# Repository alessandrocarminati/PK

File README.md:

# Password keeper 
The password keeper is a toy device for storing the personal password, and type them quickly.
The device can store up to 8 different passwords, no more than 16 chars each with 8 tags no more than 8 chars each.
One of the two buttons on the device allows the user to select the intended password and while the other allows to type it.
One two lines Hitachi HD44780 compatible display allows the user to see the tag associated with the password before typing it.
Relevant features of this project are as follows:
* The main MCU is an AVR ATTINY 85 @16MHz
* Just one MCU GPIO is used to drive the display
* The device presents itself as a keyboard, and it allows using just the USB keyboard interface to update the password DB

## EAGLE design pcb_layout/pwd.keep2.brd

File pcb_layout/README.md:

#Password keeper PCB
The current repository implements the following schema

Because it is printed by hand, an effort is made to keep it single face.

Here the routed PCB

# BOM
| ID | Name     | Package      | Qty | Designation
|----|----------|--------------|-----|-------------
|  1 | IC1      | DIL16        |   1 | 74HC595N
|  2 | IC2      | DIL08        |   1 | ATtiny85-20PU
|  3 | IC3      | DIL14        |   1 | CD40106BCN
|  4 | R1, R2   | 0207/10      |   2 | 68 $\Omega$
|  5 | R3       | 0207/10      |   1 | 33k $\Omega$
|  6 | R4       | 0207/10      |   1 | 220k $\Omega$
|  7 | R5       | 0207/10      |   1 | 560 $\Omega$ 
|  8 | R6, R7   | 0207/10      |   2 | 10k $\Omega$
|  9 | R10      | 0207/10      |   1 | 1.5k $\Omega$ 
| 10 | R11      | 0207/10      |   1 | 470 $\Omega$ 
| 11 | D1       | DO35         |   1 | 1N581
| 12 | D2, D3   | DO35         |   2 | 1N5227B-TR
| 13 | LED1     | LED5MM       |   1 | Power
| 14 | LED2     | LED5MM       |   1 | ACT
| 15 | C1       | E2-5         |   1 | 10$\mu$F
| 16 | C2, C3   | C050-024X044 |   2 | 2.2nF
| 17 | J1       | 2X07_LOCK    |   1 | Display Connector
| 18 | JP3      | USB-B-PTH    |   1 | USB-B
| 19 | JP2      | 1X02_LOCK    |   1 | Reset
| 20 | JP4      | 1X02_LOCK    |   1 | Button1
| 21 | JP5      | 1X02_LOCK    |   1 | Button2
| 22 | DISPLAY  | NA           |   1 | LM16211

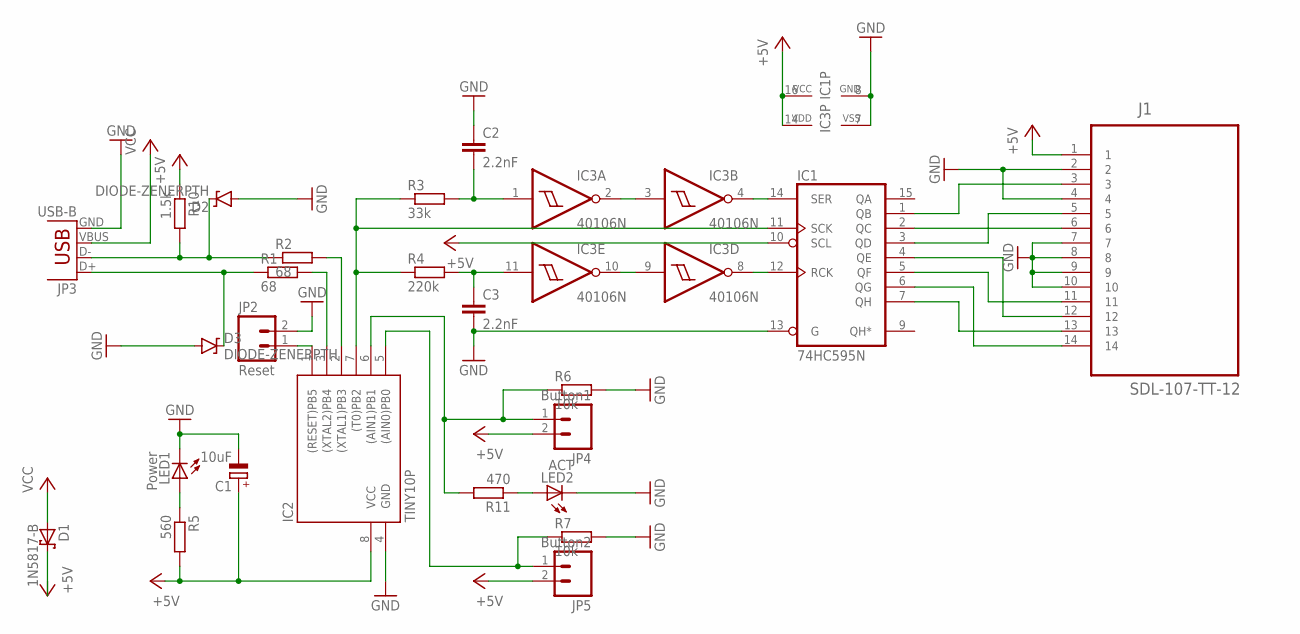
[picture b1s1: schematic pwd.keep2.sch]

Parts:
C1: 10uF; E2-5
C2, C3: 2.2nF; C050-024X044
D1: 1N5817-B; DO41-7.6
D2, D3: DIODE-ZENERPTH; DIODE-ZENER
IC1: 74HC595N; DIL16
IC2: TINY10P; DIL08
IC3: 40106N; DIL14
J1: SDL-107-TT-12; SAMTEC_SDL-107-TT-12
JP2: Reset; 1X02_LOCK
JP3: USB-B; USB-B-PTH
JP4: Button1; 1X02_LOCK
JP5: Button2; 1X02_LOCK
LED1: Power; LED5MM
LED2: ACT; LED5MM
R1, R2: 68; 0207/10
R3: 33k; 0207/10
R4: 220k; 0207/10
R5: 560; 0207/10
R6, R7: 10k; 0207/10
R10: 1.5k; 0207/10
R11: 470; 0207/10

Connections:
+5V: C1.+, D1.C, IC1.10 (SCL), IC1.16 (VCC), IC2.8 (VCC), IC3.14 (VDD), J1.1, JP4.2, JP5.2, R5.2, R10.1
GND: C1.-, C2.1, C3.2, D2.P$2 (A), D3.P$2 (A), IC1.8 (GND), IC1.13 (G), IC2.4 (GND), IC3.7 (VSS), J1.2, J1.4, J1.7, J1.8, J1.9, J1.10, JP2.2, JP3.GND, LED1.K (C), LED2.K (C), R6.2, R7.2
unnamed: IC1.7 (QH), J1.13
unnamed: IC1.6 (QG), J1.14
unnamed: IC1.5 (QF), J1.11
unnamed: IC1.4 (QE), J1.12
unnamed: IC1.3 (QD), J1.5
unnamed: IC1.2 (QC), J1.6
unnamed: IC1.1 (QB), J1.3
unnamed: D3.P$1 (C), JP3.D+, R1.1
unnamed: IC2.3 ((XTAL2)PB4), R1.2
unnamed: D2.P$1 (C), JP3.D-, R2.1, R10.2
unnamed: IC2.2 ((XTAL1)PB3), R2.2
unnamed: IC2.1 ((RESET)PB5), JP2.1
unnamed: LED2.A, R11.1
unnamed: LED1.A, R5.1
unnamed: IC1.11 (SCK), IC2.7 ((T0)PB2), R3.1, R4.1
unnamed: C3.1, IC3.11 (I), R4.2
unnamed: C2.2, IC3.1 (I), R3.2
unnamed: IC2.6 ((AIN1)PB1), JP4.1, R6.1, R11.2
unnamed: IC3.2 (O), IC3.3 (I)
unnamed: IC2.5 ((AIN0)PB0), JP5.1, R7.1
unnamed: IC1.14 (SER), IC3.4 (O)
unnamed: IC1.12 (RCK), IC3.8 (O)
unnamed: IC3.9 (I), IC3.10 (O)
VCC: D1.A, JP3.VBUS

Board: 2 copper layers, 25 parts (0 on the bottom side), 26 nets, no tracks yet.

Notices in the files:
parts and their libraries:
SparkFun-DiscreteSemi: Licensing: Creative Commons ShareAlike 4.0 International - https://creativecommons.org/licenses/by-sa/4.0
